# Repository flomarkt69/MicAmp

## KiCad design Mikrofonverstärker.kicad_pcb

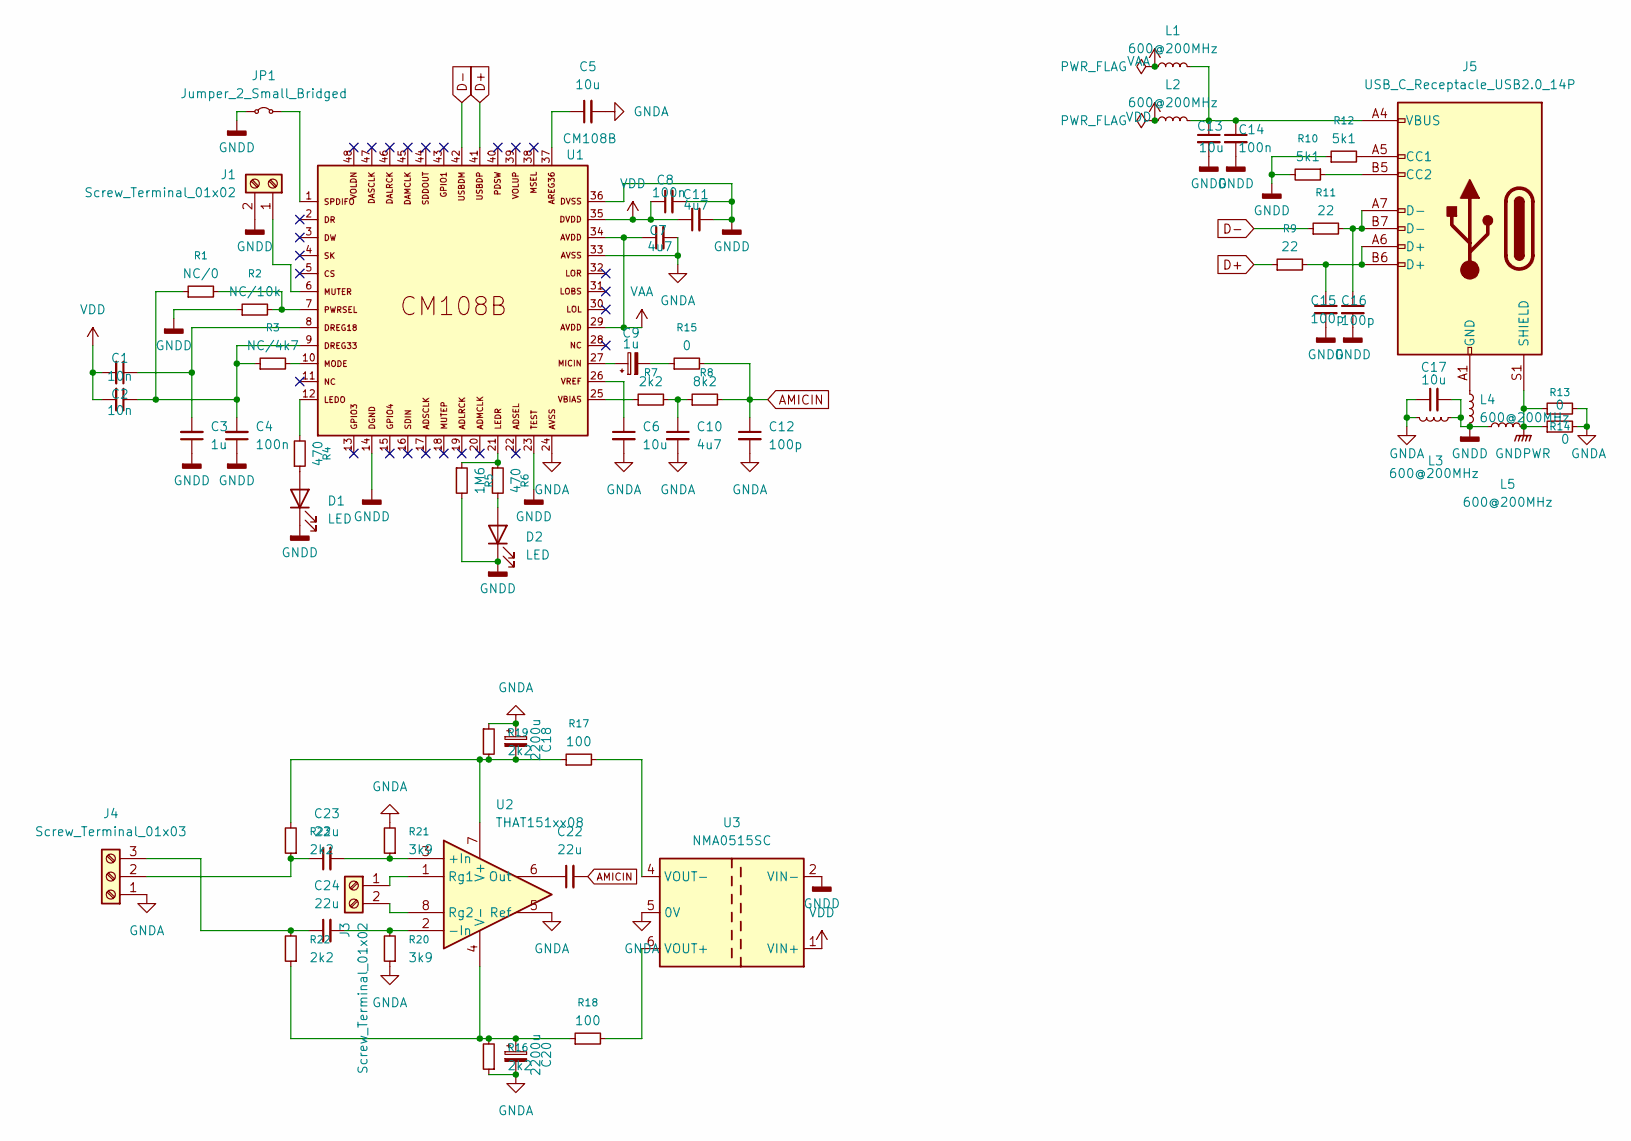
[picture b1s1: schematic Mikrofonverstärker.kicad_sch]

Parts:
C1, C2: 10n; C_0402_1005Metric
C3: 1u; C_0402_1005Metric
C4, C8, C14: 100n; C_0402_1005Metric
C5, C6, C13, C17: 10u; C_0402_1005Metric
C7, C10, C11: 4u7; C_0402_1005Metric
C9: 1u; C_0805_2012Metric
C12, C15, C16: 100p; C_0402_1005Metric
C18, C20: 2200u; CP_Radial_D10.0mm_P5.00mm
C22, C23, C24: 22u; C_0805_2012Metric
D1, D2: LED; LED_0402_1005Metric
J1, J3: Screw_Terminal_01x02; DB125-2.54-2P
J4: Screw_Terminal_01x03; DB125-2.54-3P
J5: USB_C_Receptacle_USB2.0_14P; USB_C_Receptacle_Palconn_UTC16-G
JP1: Jumper_2_Small_Bridged; TestPoint_2Pads_Pitch2.54mm_Drill0.8mm
L1, L2, L3, L4, L5: 600@200MHz; L_0402_1005Metric
R1: NC/0; R_0402_1005Metric
R2: NC/10k; R_0402_1005Metric
R3: NC/4k7; R_0402_1005Metric
R4, R6: 470; R_0402_1005Metric
R5: 1M6; R_0402_1005Metric
R7: 2k2; R_0402_1005Metric
R8: 8k2; R_0402_1005Metric
R9, R11: 22; R_0402_1005Metric
R10, R12: 5k1; R_0402_1005Metric
R13, R14, R15: 0; R_0402_1005Metric
R16, R19, R22, R23: 2k2; R_0805_2012Metric
R17, R18: 100; R_0805_2012Metric
R20, R21: 3k9; R_0805_2012Metric
U1: CM108B; TQFP48
U2: THAT151xx08; DIP-8_W7.62mm
U3: NMA0515SC; Converter_DCDC_Murata_NMAxxxxSC_THT

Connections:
AMICIN: C12.1, C22.2, R8.2, R15.2
D+: R9.1, U1.41
D-: R11.1, U1.42
GNDA: C5.2, C6.2, C7.2, C10.2, C12.2, C17.1, C18.1, C20.2, J4.1, L3.2, R13.2, R14.2, R16.1, R19.1, R20.1, R21.2, U1.24, U1.33, U2.5 (Ref), U3.5 (0V)
GNDD: C3.1, C4.1, C8.2, C11.2, C13.2, C14.2, C15.2, C16.2, C17.2, D1.1 (K), D2.1 (K), J1.2, JP1.1 (A), L3.1, L4.2, L5.1, R2.1, R5.2, R10.2, R12.1, U1.14, U1.23, U1.36, U3.2 (VIN-)
GNDPWR: J5.S1 (SHIELD), L5.2, R13.1, R14.1
unnamed: C1.1, C3.2, U1.8
unnamed: C2.1, C4.2, R1.1, R3.1, U1.9
unnamed: C5.1, U1.37
unnamed: C6.1, U1.26
unnamed: C9.1, U1.27
unnamed: C9.2, R15.1
unnamed: C10.1, R7.2, R8.1
unnamed: C13.1, C14.1, J5.A4 (VBUS), J5.A9 (VBUS), J5.B4 (VBUS), J5.B9 (VBUS), L1.2, L2.2
unnamed: C15.1, J5.A6 (D+), J5.B6 (D+), R9.2
unnamed: C16.1, J5.A7 (D-), J5.B7 (D-), R11.2
unnamed: D1.2 (A), R4.1
unnamed: D2.2 (A), R6.2
unnamed: J1.1, U1.6
unnamed: J3.1, U2.1 (Rg1)
unnamed: J3.2, U2.8 (Rg2)
unnamed: C23.1, J4.2, R23.1
unnamed: C24.1, J4.3, R22.2
unnamed: J5.A5 (CC1), R12.2
unnamed: J5.B5 (CC2), R10.1
unnamed: J5.A1 (GND), J5.A12 (GND), J5.B1 (GND), J5.B12 (GND), L4.1
unnamed: JP1.2 (B), U1.1
unnamed: R1.2, R2.2, U1.7
unnamed: R3.2, U1.10
unnamed: R4.2, U1.12
unnamed: R5.1, R6.1, U1.21
unnamed: R7.1, U1.25
unnamed: C23.2, R21.1, U2.3 (+In)
unnamed: C24.2, R20.2, U2.2 (-In)
unnamed: C22.1, U2.6 (Out)
unnamed: C18.2, R17.1, R19.2, R23.2, U2.7 (V+)
unnamed: C20.1, R16.2, R18.1, R22.1, U2.4 (V-)
unnamed: R18.2, U3.6 (VOUT+)
unnamed: R17.2, U3.4 (VOUT-)
VAA: C7.1, L1.1, U1.29, U1.34
VDD: C1.2, C2.2, C8.1, C11.1, L2.1, U1.35, U3.1 (VIN+)

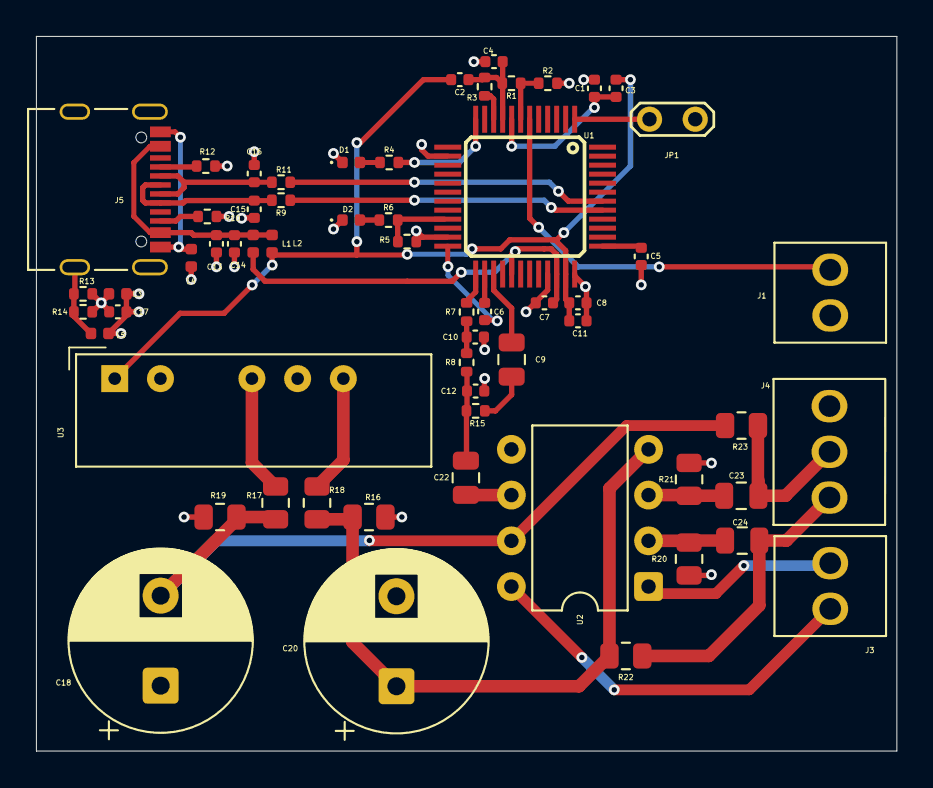
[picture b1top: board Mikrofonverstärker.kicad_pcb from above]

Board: 2 copper layers, 47.8 x 39.7 mm, 60 parts (0 on the bottom side), 41 nets.

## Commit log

2026-02-09 schaltung ist fertig maschalla
2026-02-09 final layout
2026-02-09 fertiges projekt
2026-02-09 almost perfection
2026-02-09 autorouting ausprobiert
